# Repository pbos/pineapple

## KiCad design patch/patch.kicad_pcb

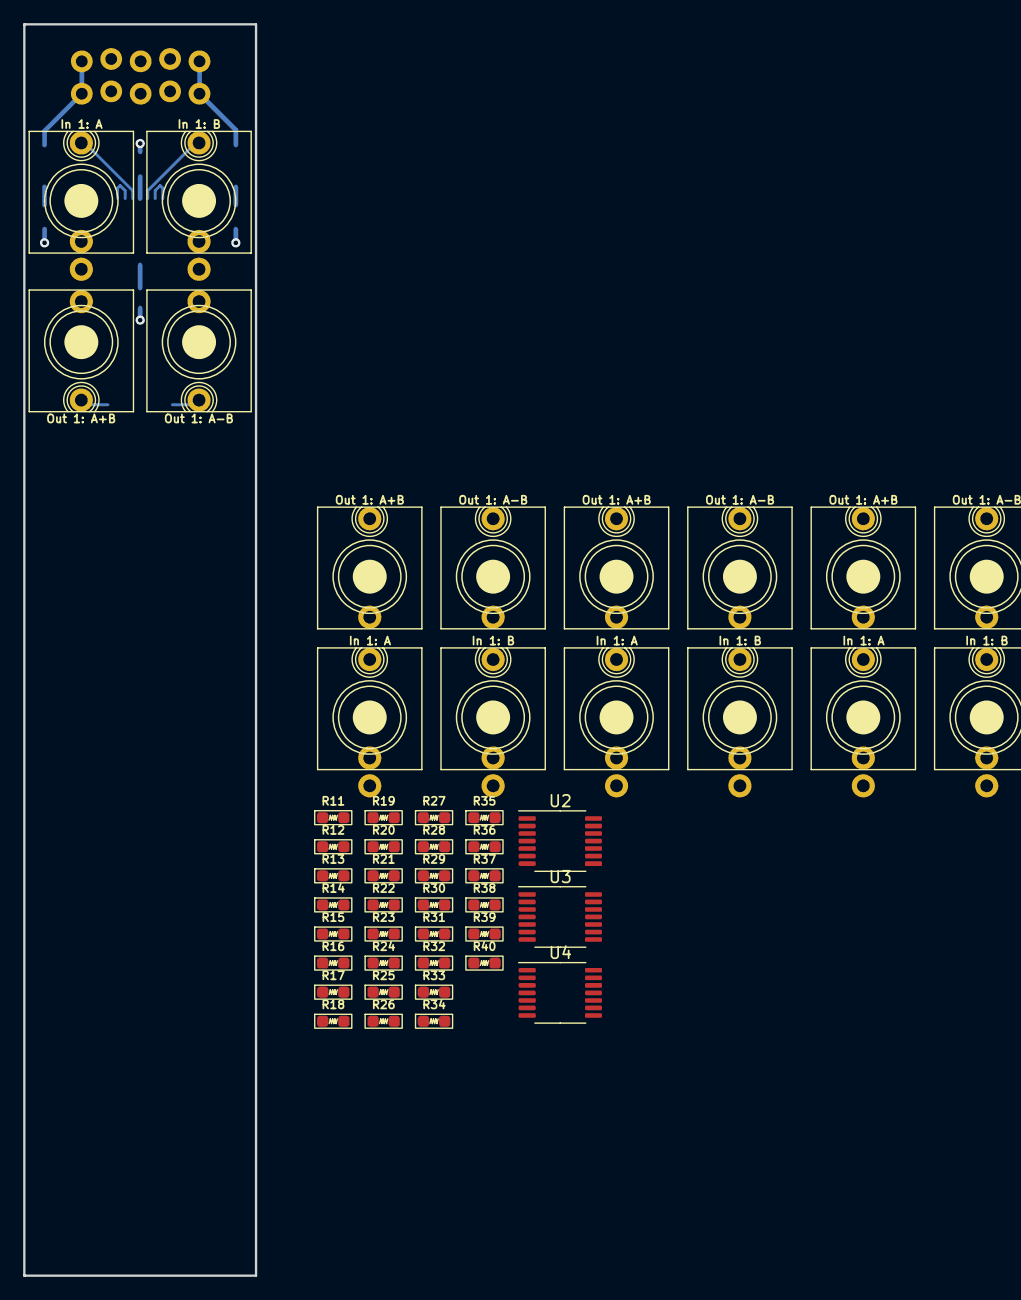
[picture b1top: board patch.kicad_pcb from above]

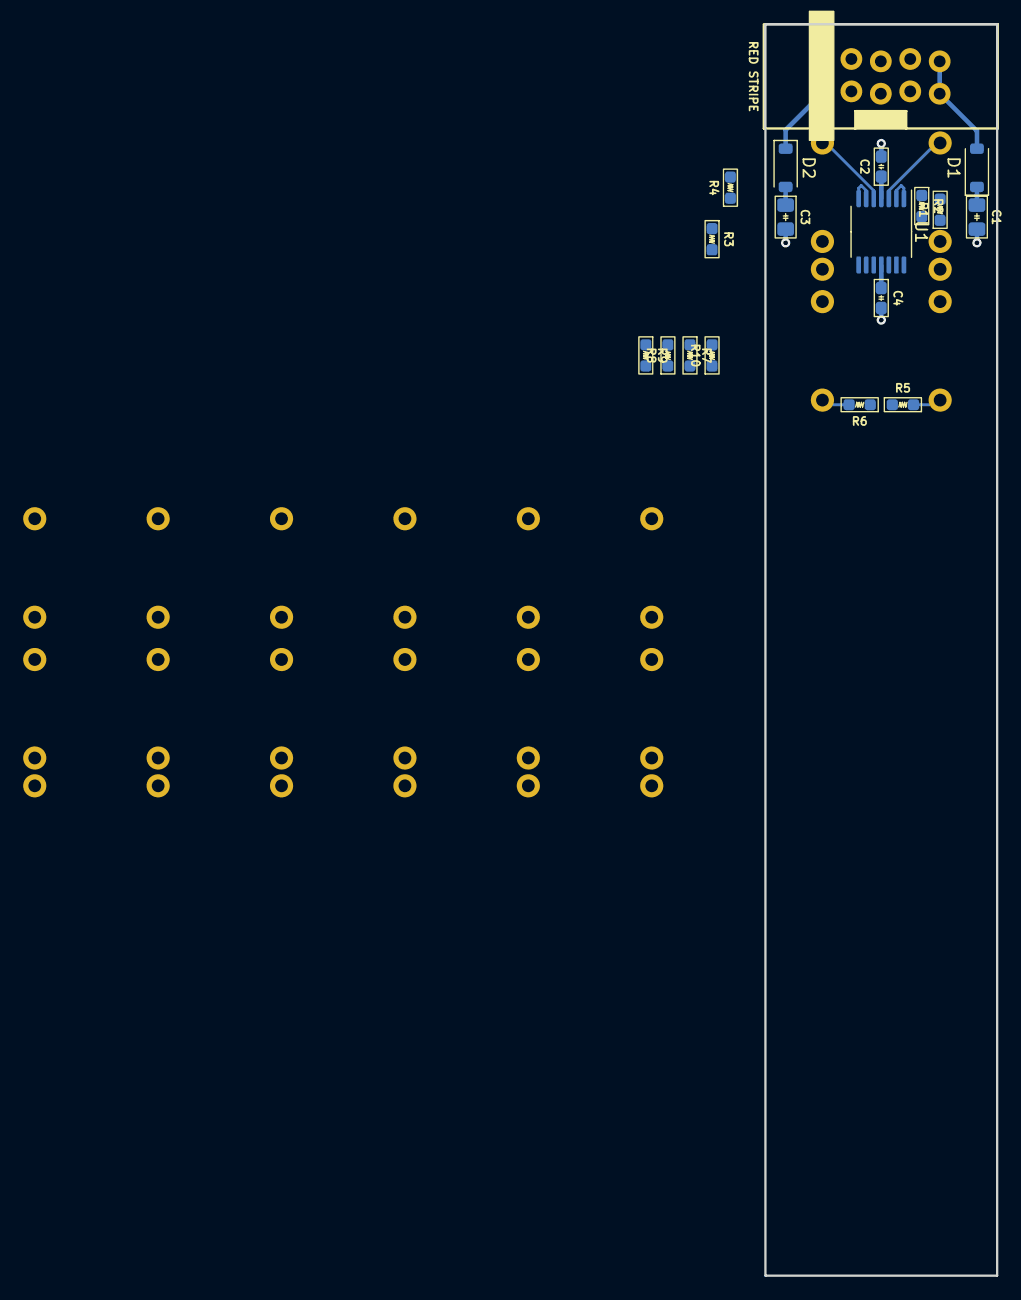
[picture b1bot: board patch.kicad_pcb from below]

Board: 4 copper layers, 20.0 x 108.0 mm, 67 parts (18 on the bottom side), 53 nets.

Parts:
C1, C3: 10u; C_0805_HandSolder
C2, C4: 100n; C_0603_HandSolder
D1, D2: 30V; D_SOD-123
J1: Eurorack_Power; Eurorack_Power_2x5_Shrouded_Lock
J2, J6, J10, J14: In 1: A; AudioJack_WQP518MA_Compact_S
J3, J7, J11, J15: In 1: B; AudioJack_WQP518MA_Compact_S
J4, J8, J12, J16: Out 1: A+B; AudioJack_WQP518MA_No_S
J5, J9, J13, J17: Out 1: A-B; AudioJack_WQP518MA_No_S
R1, R2, R3, R4, R7, R8, R9, R10, R11, R12, R13, R14, R17, R18, R19, R20, R21, R22, R23, R24, R27, R28, R29, R30, R31, R32, R33, R34, R37, R38, R39, R40: 10k; R_0603_HandSolder
R5, R6, R15, R16, R25, R26, R35, R36: 51R; R_0603_HandSolder
U1, U2, U3, U4: OPA4991; TSSOP-14_4.4x5mm_P0.65mm

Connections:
GND: C1.2, C2.2, C3.2, C4.2, J1.3 (GND), J1.4 (GND), J1.5 (GND), J1.6 (GND), J1.7 (GND), J1.8 (GND), J2.S (Sleeve), J2.TN (Tip_normalize), J3.S (Sleeve), J3.TN (Tip_normalize), J6.S (Sleeve), J7.S (Sleeve), J10.S (Sleeve), J11.S (Sleeve), J14.S (Sleeve), J15.S (Sleeve), R8.1, R10.1, R18.1, R20.1, R28.1, R30.1, R38.1, R40.1
unnamed: D1.2 (A), J1.9 (+12V), J1.10 (+12V)
unnamed: D2.1 (K), J1.1 (-12V), J1.2 (-12V)
unnamed: J2.T (Tip), J6.TN (Tip_normalize), U1.3 (+)
unnamed: J3.T (Tip), U1.5 (+)
unnamed: J4.T (Tip), R5.2
unnamed: J5.T (Tip), R6.2
unnamed: J7.T (Tip), U2.10 (+)
unnamed: J8.T (Tip), R15.2
unnamed: J9.T (Tip), R16.2
unnamed: J10.T (Tip), J11.TN (Tip_normalize), J14.TN (Tip_normalize), U3.5 (+)
unnamed: J6.T (Tip), J7.TN (Tip_normalize), J10.TN (Tip_normalize), U2.5 (+)
unnamed: J11.T (Tip), U3.10 (+)
unnamed: J12.T (Tip), R25.2
unnamed: J13.T (Tip), R26.2
unnamed: J14.T (Tip), J15.TN (Tip_normalize), U4.5 (+)
unnamed: J15.T (Tip), U4.10 (+)
unnamed: J16.T (Tip), R35.2
unnamed: J17.T (Tip), R36.2
unnamed: R5.1, R7.2, U1.14
unnamed: R6.1, R9.2, U1.8
unnamed: R15.1, R17.2, U2.1
unnamed: R16.1, R19.2, U2.14
unnamed: R25.1, R27.2, U3.1
unnamed: R26.1, R29.2, U3.14
unnamed: R35.1, R37.2, U4.1
unnamed: R36.1, R39.2, U4.14
unnamed: R1.2, R4.2, U1.1, U1.2 (-)
unnamed: R2.1, R3.2, U1.6 (-), U1.7
unnamed: R4.1, R8.2, U1.10 (+)
unnamed: R3.1, R9.1, U1.9 (-)
unnamed: R1.1, R2.2, U1.12 (+)
unnamed: R7.1, R10.2, U1.13 (-)
unnamed: R12.1, R13.2, U2.3 (+)
unnamed: R17.1, R20.2, U2.2 (-)
unnamed: R11.2, R12.2, U2.6 (-), U2.7
unnamed: R13.1, R14.2, U2.8, U2.9 (-)
unnamed: R11.1, R18.2, U2.12 (+)
unnamed: R14.1, R19.1, U2.13 (-)
unnamed: R22.1, R23.2, U3.3 (+)
unnamed: R27.1, R30.2, U3.2 (-)
unnamed: R21.2, R22.2, U3.6 (-), U3.7
unnamed: R23.1, R24.2, U3.8, U3.9 (-)
unnamed: R21.1, R28.2, U3.12 (+)
unnamed: R24.1, R29.1, U3.13 (-)
unnamed: R32.1, R33.2, U4.3 (+)
unnamed: R37.1, R40.2, U4.2 (-)
unnamed: R31.2, R32.2, U4.6 (-), U4.7
unnamed: R33.1, R34.2, U4.8, U4.9 (-)
unnamed: R31.1, R38.2, U4.12 (+)
unnamed: R34.1, R39.1, U4.13 (-)
VCC: C1.1, C2.1, D1.1 (K), U1.4 (V+)
VEE: C3.1, C4.1, D2.2 (A), U1.11 (V-)

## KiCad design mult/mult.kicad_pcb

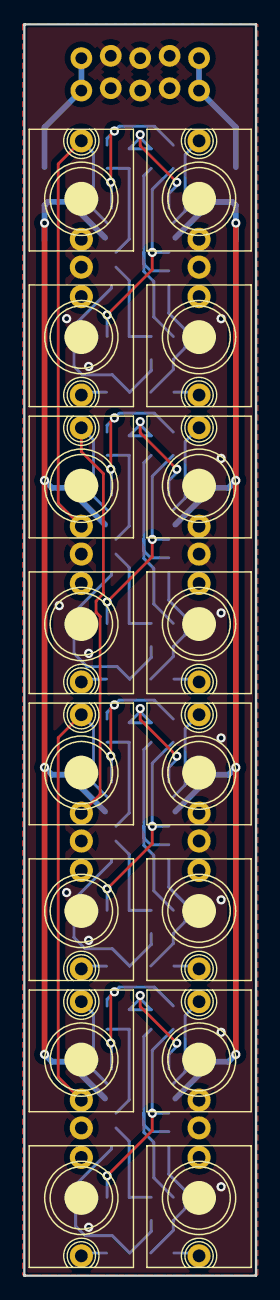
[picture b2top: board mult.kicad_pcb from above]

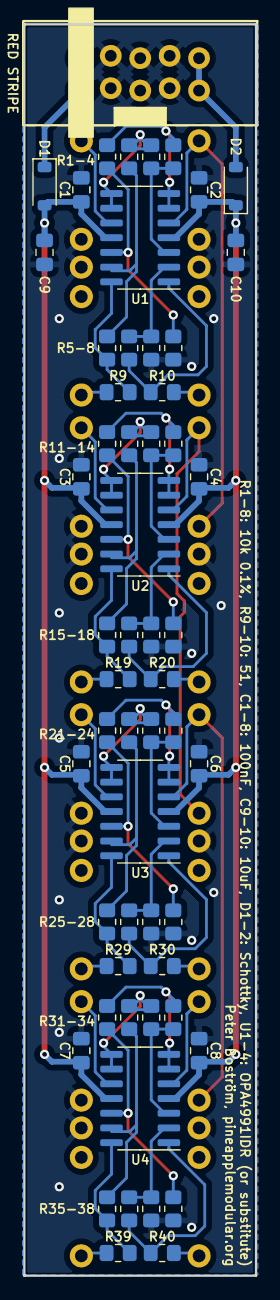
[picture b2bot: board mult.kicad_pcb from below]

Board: 2 copper layers, 20.0 x 108.0 mm, 73 parts (57 on the bottom side), 53 nets.

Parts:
C1, C2, C3, C4, C5, C6, C7, C8: 100nF; C_0805_2012Metric_Pad1.18x1.45mm_HandSolder
C9, C10: 10uF; C_0805_2012Metric_Pad1.18x1.45mm_HandSolder
D1, D2: D_Schottky; D_SOD-123
J1, J2, J5, J6, J9, J10, J13, J14: Eurorack_Mono_Jack; AudioJack_WQP518MA_Compact_S
J3, J4, J7, J8, J11, J12, J15, J16: Eurorack_Mono_Jack_No_S; AudioJack_WQP518MA_No_S
J17: Eurorack_Power; Eurorack_Power_2x5_Shrouded_Lock
R1, R2, R3, R4, R5, R6, R7, R8, R11, R12, R13, R14, R15, R16, R17, R18, R21, R22, R23, R24, R25, R26, R27, R28, R31, R32, R33, R34, R35, R36, R37, R38: 10k; R_0805_2012Metric_Pad1.20x1.40mm_HandSolder
R9, R10, R19, R20, R29, R30, R39, R40: 51; R_0805_2012Metric_Pad1.20x1.40mm_HandSolder
U1, U2, U3, U4: OPA1679; SOIC-14_3.9x8.7mm_P1.27mm

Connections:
/channel 1/tip in (a): J1.T (Tip), J5.TN (Tip_normalize), U1.5 (+)
/channel 2/tip in (a): J5.T (Tip), J9.TN (Tip_normalize), U2.5 (+)
/channel 3/tip in (a): J9.T (Tip), J13.TN (Tip_normalize), U3.5 (+)
/channel 4/tip in (a): J13.T (Tip), U4.5 (+)
GND: C1.2, C2.2, C3.2, C4.2, C5.2, C6.2, C7.2, C8.2, C9.2, C10.2, J1.S (Sleeve), J1.TN (Tip_normalize), J2.S (Sleeve), J2.TN (Tip_normalize), J5.S (Sleeve), J6.S (Sleeve), J6.TN (Tip_normalize), J9.S (Sleeve), J10.S (Sleeve), J10.TN (Tip_normalize), J13.S (Sleeve), J14.S (Sleeve), J14.TN (Tip_normalize), J17.3 (GND), J17.4 (GND), J17.5 (GND), J17.6 (GND), J17.7 (GND), J17.8 (GND), R7.1, R8.1, R17.1, R18.1, R27.1, R28.1, R37.1, R38.1
unnamed: D1.1 (K), J17.1 (-12V), J17.2 (-12V)
unnamed: D2.2 (A), J17.9 (+12V), J17.10 (+12V)
unnamed: J2.T (Tip), U1.10 (+)
unnamed: J3.T (Tip), R10.2
unnamed: J4.T (Tip), R9.2
unnamed: J6.T (Tip), U2.10 (+)
unnamed: J7.T (Tip), R20.2
unnamed: J8.T (Tip), R19.2
unnamed: J10.T (Tip), U3.10 (+)
unnamed: J11.T (Tip), R30.2
unnamed: J12.T (Tip), R29.2
unnamed: J14.T (Tip), U4.10 (+)
unnamed: J15.T (Tip), R40.2
unnamed: J16.T (Tip), R39.2
unnamed: R5.2, R9.1, U1.14
unnamed: R6.2, R10.1, U1.1
unnamed: R15.2, R19.1, U2.14
unnamed: R16.2, R20.1, U2.1
unnamed: R25.2, R29.1, U3.14
unnamed: R26.2, R30.1, U3.1
unnamed: R35.2, R39.1, U4.14
unnamed: R36.2, R40.1, U4.1
unnamed: R3.2, R4.1, U1.3 (+)
unnamed: R6.1, R7.2, U1.2 (-)
unnamed: R1.2, R4.2, U1.6 (-), U1.7
unnamed: R2.2, R3.1, U1.8, U1.9 (-)
unnamed: R1.1, R8.2, U1.12 (+)
unnamed: R2.1, R5.1, U1.13 (-)
unnamed: R13.2, R14.1, U2.3 (+)
unnamed: R16.1, R17.2, U2.2 (-)
unnamed: R11.2, R14.2, U2.6 (-), U2.7
unnamed: R12.2, R13.1, U2.8, U2.9 (-)
unnamed: R11.1, R18.2, U2.12 (+)
unnamed: R12.1, R15.1, U2.13 (-)
unnamed: R23.2, R24.1, U3.3 (+)
unnamed: R26.1, R27.2, U3.2 (-)
unnamed: R21.2, R24.2, U3.6 (-), U3.7
unnamed: R22.2, R23.1, U3.8, U3.9 (-)
unnamed: R21.1, R28.2, U3.12 (+)
unnamed: R22.1, R25.1, U3.13 (-)
unnamed: R33.2, R34.1, U4.3 (+)
unnamed: R36.1, R37.2, U4.2 (-)
unnamed: R31.2, R34.2, U4.6 (-), U4.7
unnamed: R32.2, R33.1, U4.8, U4.9 (-)
unnamed: R31.1, R38.2, U4.12 (+)
unnamed: R32.1, R35.1, U4.13 (-)
VCC: C2.1, C4.1, C6.1, C8.1, C10.1, D2.1 (K), U1.4 (V+), U2.4 (V+), U3.4 (V+), U4.4 (V+)
VEE: C1.1, C3.1, C5.1, C7.1, C9.1, D1.2 (A), U1.11 (V-), U2.11 (V-), U3.11 (V-), U4.11 (V-)

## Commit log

2023-08-02 Add -backups to .gitignore
2023-08-02 Add .kicad_prl to .gitignore
2023-08-02 mult: Add skeleton project
2023-08-02 mult: Add A+B per-channel circuit
    Jacks should be added to the channel schematics after importing a good
    third-party schematic library.
2023-08-02 Add winterbloom_kicad_library submodule
2023-08-02 mult: Add jacks and bypass caps to channel
2023-08-02 mult: Populate root schematic, add LEDs
    Placeholder Eurorack_Power is placed but missing diode + caps. Should
    probably be replaced with reusable power subschematic.
2023-08-02 mult: Add LED TODOs, change resistor values to 680
2023-08-02 mult: Add TSSOP footprint to LM324
2023-08-02 mult: Replace v+ and v- labels with VCC,VEE
    This removes a lot of unnecessary wires as well. Also updating LED
    resistors to 1k to match Mutable Instruments Links and resolving TODO.
2023-08-02 mult: Add winterbloom footprint library
2023-08-02 Add _autosave* to .gitignore
2023-08-02 Pull third_party/winterbloom_kicad_library
    This brings in the correct footprint for Eurorack_Power.
2023-08-02 mult: Add power subschematic
2023-08-02 mult: Manually assign references, grouped by value
2023-08-02 mult: Assign footprints
2023-08-02 mult: Import schematic into PCB
2023-08-02 mult: Misc partial progress
    At least since last commit:
    * New LEDs (no dual unit)
    * Jack placement, share sleeve pin
    * Board fit within 20x108mm
2023-08-02 mult: Replicate all channel PCB layouts
    To do this the Replicate Layout plugin was heavily used. Post-replicate
    moved channel 2's op amp to leave room for the LED op-amp.
    Starting to layout some LED capacitors and route power.
2023-08-02 mult: Reorder channel schematic to match layout
2023-08-02 mult: Remove LEDs, add A-B output
2023-08-02 mult: Update resistor references
2023-08-02 mult: Place power diodes and caps closer to center
2023-08-02 mult: Replace OPA4917 with OPA1697
    This seems reasonable performance (2mV offset max, audio op amp etc) and
    significantly lower cost.
2023-08-02 mult: Initial board routed, all items connected
    Still expecting to make major changes this looks like mostly-random item
    placements.
2023-08-02 mult: Progress rerouting easier layout
2023-08-02 mult: Finish first layout pass, passes DRC errors
2023-08-02 mult: Move power diodes closer to header
2023-08-02 mult: Move diodes and caps away from jack pads
2023-08-02 mult: Add board constraints
    No rerouting necessary in this step (per DRC) but this makes sure the
    copper doesn't run all the way to the board edge.
2023-08-02 mult: Reassign reference designators
    This follows visual placement (left to right, top to bottom), except for
    bulk capacitors which are enumerated left to right after bypass caps.
2023-08-02 mult: Add 0.5mm power traces
    Not sure if this matters at all, but can't hurt.
2023-08-02 mult: Initial silkscreen
2023-08-02 mult: Not sure what I did, minor PCB changes
2023-08-02 mult: Add components and name to silkscreen
2023-08-03 mult: Route power away from board edges
    Also drive-by moving power diode and caps so that the D1,D2 text is
    visible after parts are placed.
2024-02-13 Pull third_party/winterbloom_kicad_library
2024-02-13 patch: Add empty project
2024-02-13 patch: Add the first channel (A+B, A-B)
    This is done first to get feedback on a single channel before laying out
    the rest.
2024-02-13 Pull third_party/winterbloom_kicad_library
    This brings in a fix for WQP518MA_Compact_S without LongPads from
    https://github.com/wntrblm/winterbloom_kicad_library/pull/3.
2024-02-25 Patch: Start of feedback, more channels
    Addressed some feedback, switched to TSSOP/0603 to get better margins.
    Started on more channels to make sure the jack and part placement is OK.
